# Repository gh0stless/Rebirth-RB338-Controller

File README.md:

# Rebirth-RB338-Controller
an ulimate MIDI controller for Rebirth RB-338

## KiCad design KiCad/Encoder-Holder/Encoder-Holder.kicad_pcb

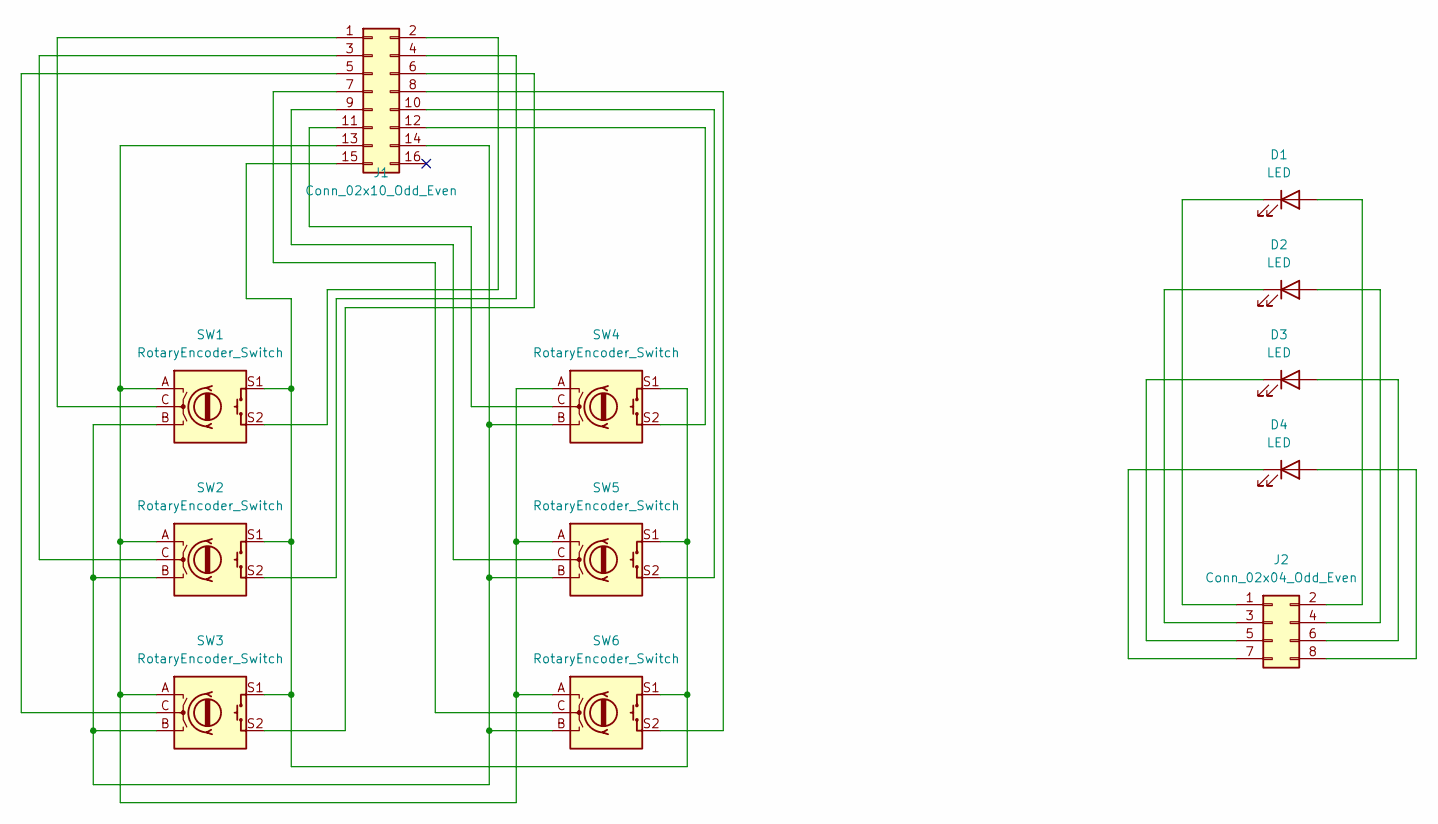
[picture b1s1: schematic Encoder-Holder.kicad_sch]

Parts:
D1, D2, D3, D4: LED; LED_D3.0mm
J1: Conn_02x10_Odd_Even; PinHeader_2x08_P2.54mm_Horizontal
J2: Conn_02x04_Odd_Even; PinHeader_2x04_P2.54mm_Horizontal
SW1, SW2, SW3, SW4, SW5, SW6: RotaryEncoder_Switch; RotaryEncoder_Alps_EC11E-Switch_Vertical_H20mm

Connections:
unnamed: D1.2 (A), J2.2
unnamed: D1.1 (K), J2.1
unnamed: D2.2 (A), J2.4
unnamed: D2.1 (K), J2.3
unnamed: D3.2 (A), J2.6
unnamed: D3.1 (K), J2.5
unnamed: D4.2 (A), J2.8
unnamed: D4.1 (K), J2.7
unnamed: J1.1, SW1.C
unnamed: J1.2, SW1.S2
unnamed: J1.3, SW2.C
unnamed: J1.4, SW2.S2
unnamed: J1.5, SW3.C
unnamed: J1.6, SW3.S2
unnamed: J1.7, SW6.C
unnamed: J1.8, SW6.S2
unnamed: J1.9, SW5.C
unnamed: J1.10, SW5.S2
unnamed: J1.11, SW4.C
unnamed: J1.12, SW4.S2
unnamed: J1.13, SW1.A, SW2.A, SW3.A, SW4.A, SW5.A, SW6.A
unnamed: J1.14, SW1.B, SW2.B, SW3.B, SW4.B, SW5.B, SW6.B
unnamed: J1.15, SW1.S1, SW2.S1, SW3.S1, SW4.S1, SW5.S1, SW6.S1

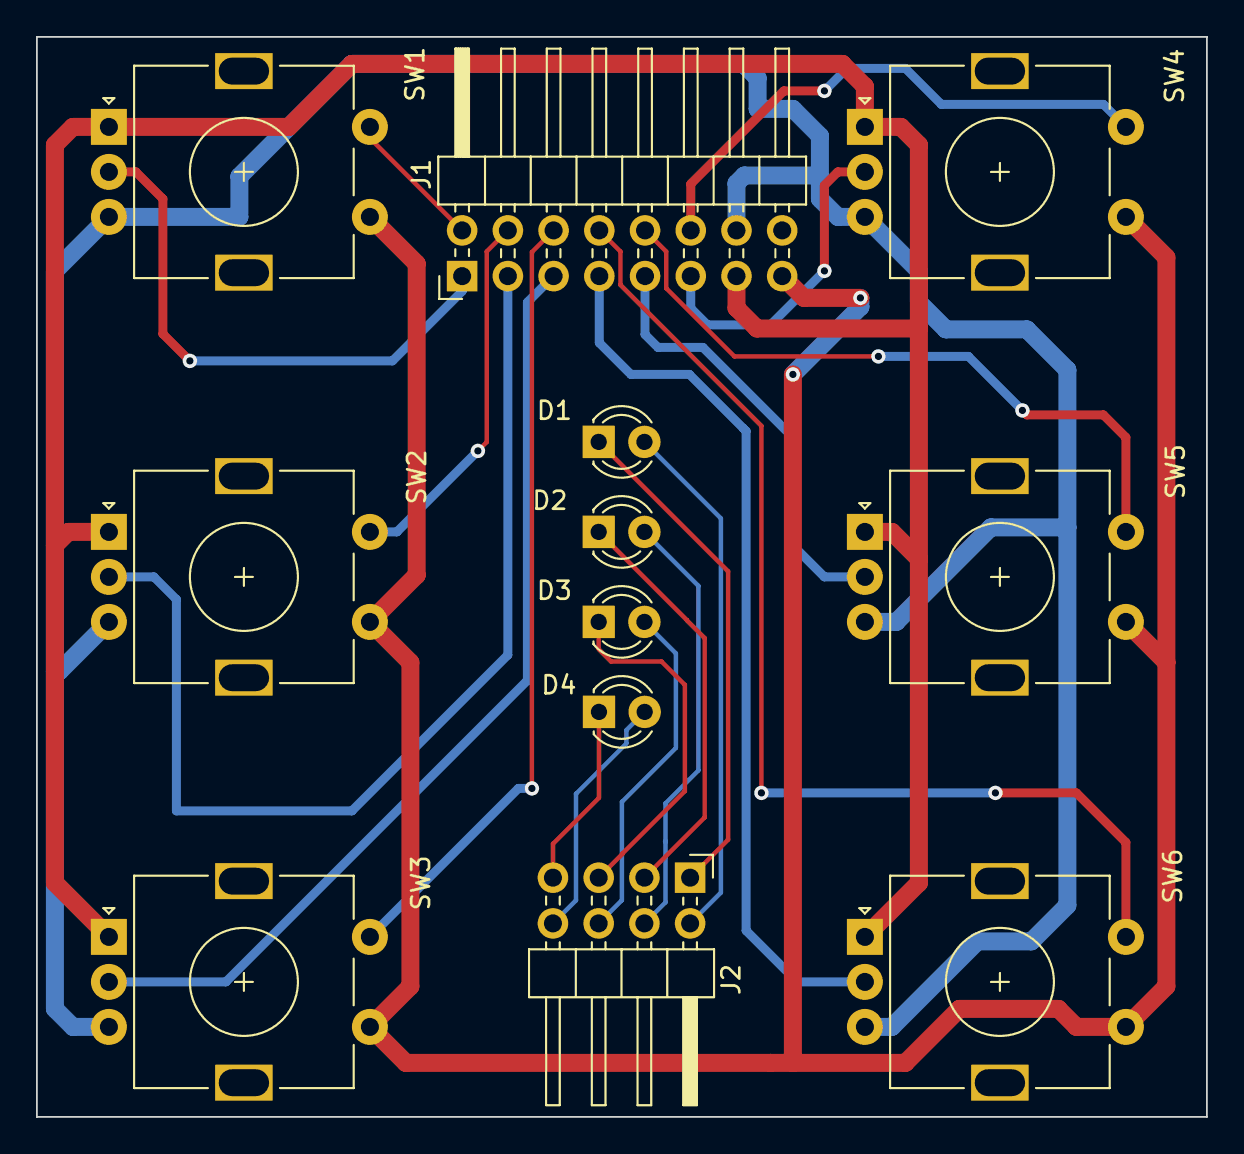
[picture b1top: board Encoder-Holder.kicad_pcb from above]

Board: 2 copper layers, 65.0 x 60.0 mm, 12 parts (0 on the bottom side), 23 nets.

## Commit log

2025-01-18 readme
2025-01-18 readme fix
2025-01-18 add Max files
2025-07-03 Sticker
2025-07-11 Release
